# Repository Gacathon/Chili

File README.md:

# Lisence

CC BY-NC-SA 3.0

# Chili
Cherry G80-3000 Keyboard layout

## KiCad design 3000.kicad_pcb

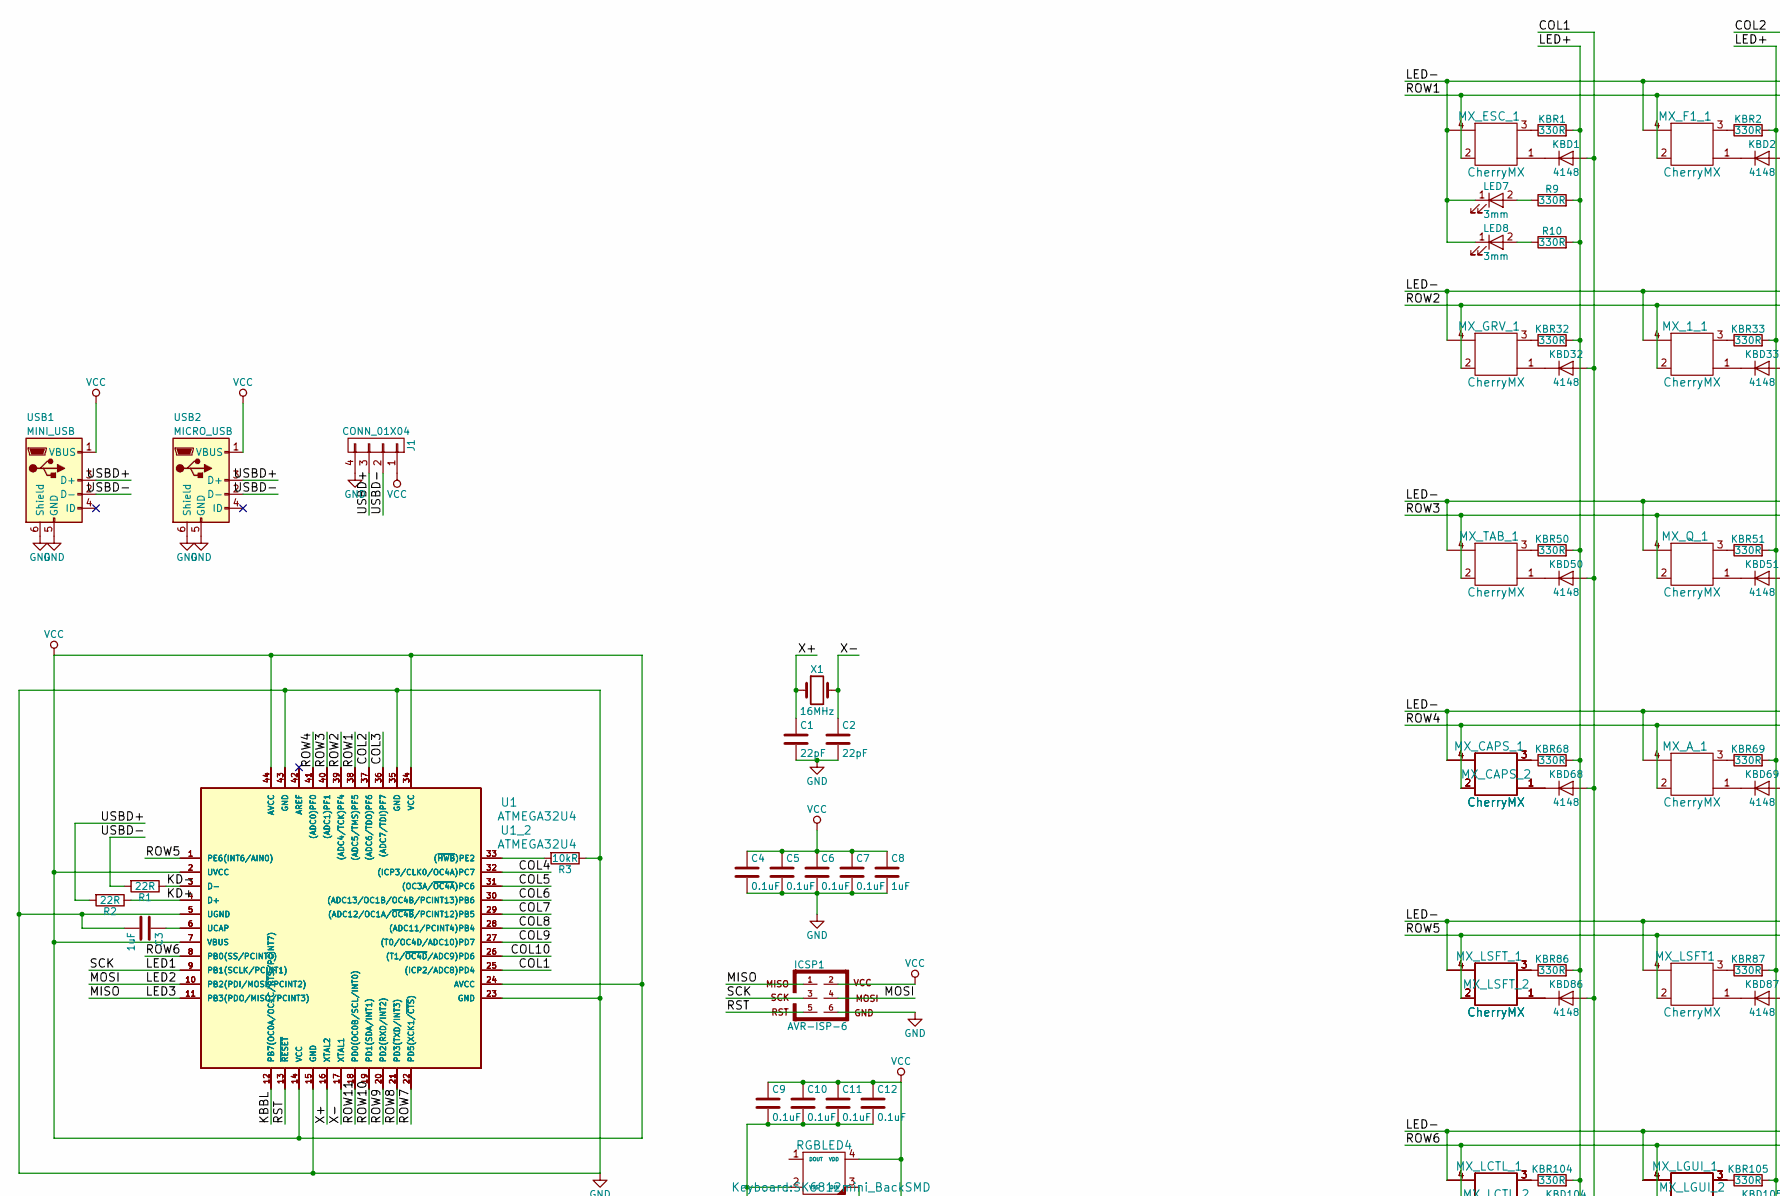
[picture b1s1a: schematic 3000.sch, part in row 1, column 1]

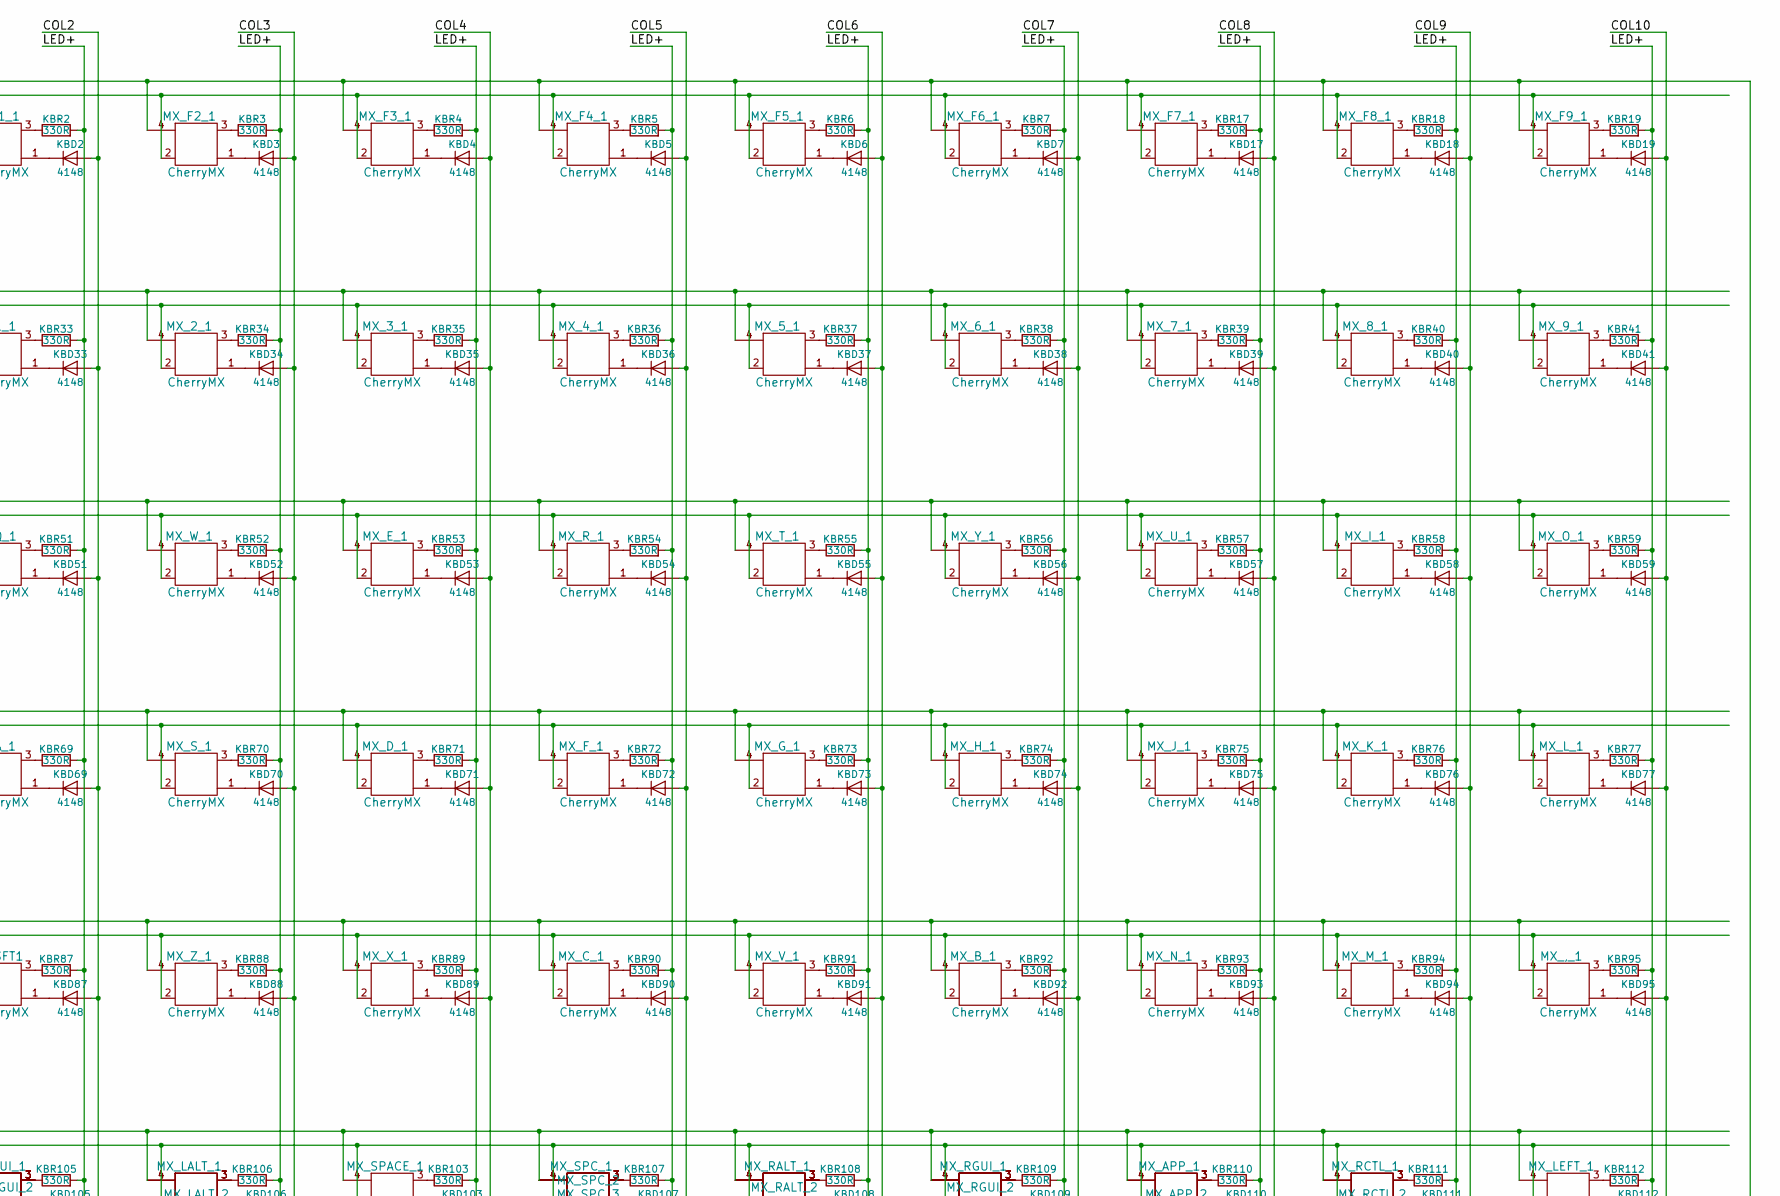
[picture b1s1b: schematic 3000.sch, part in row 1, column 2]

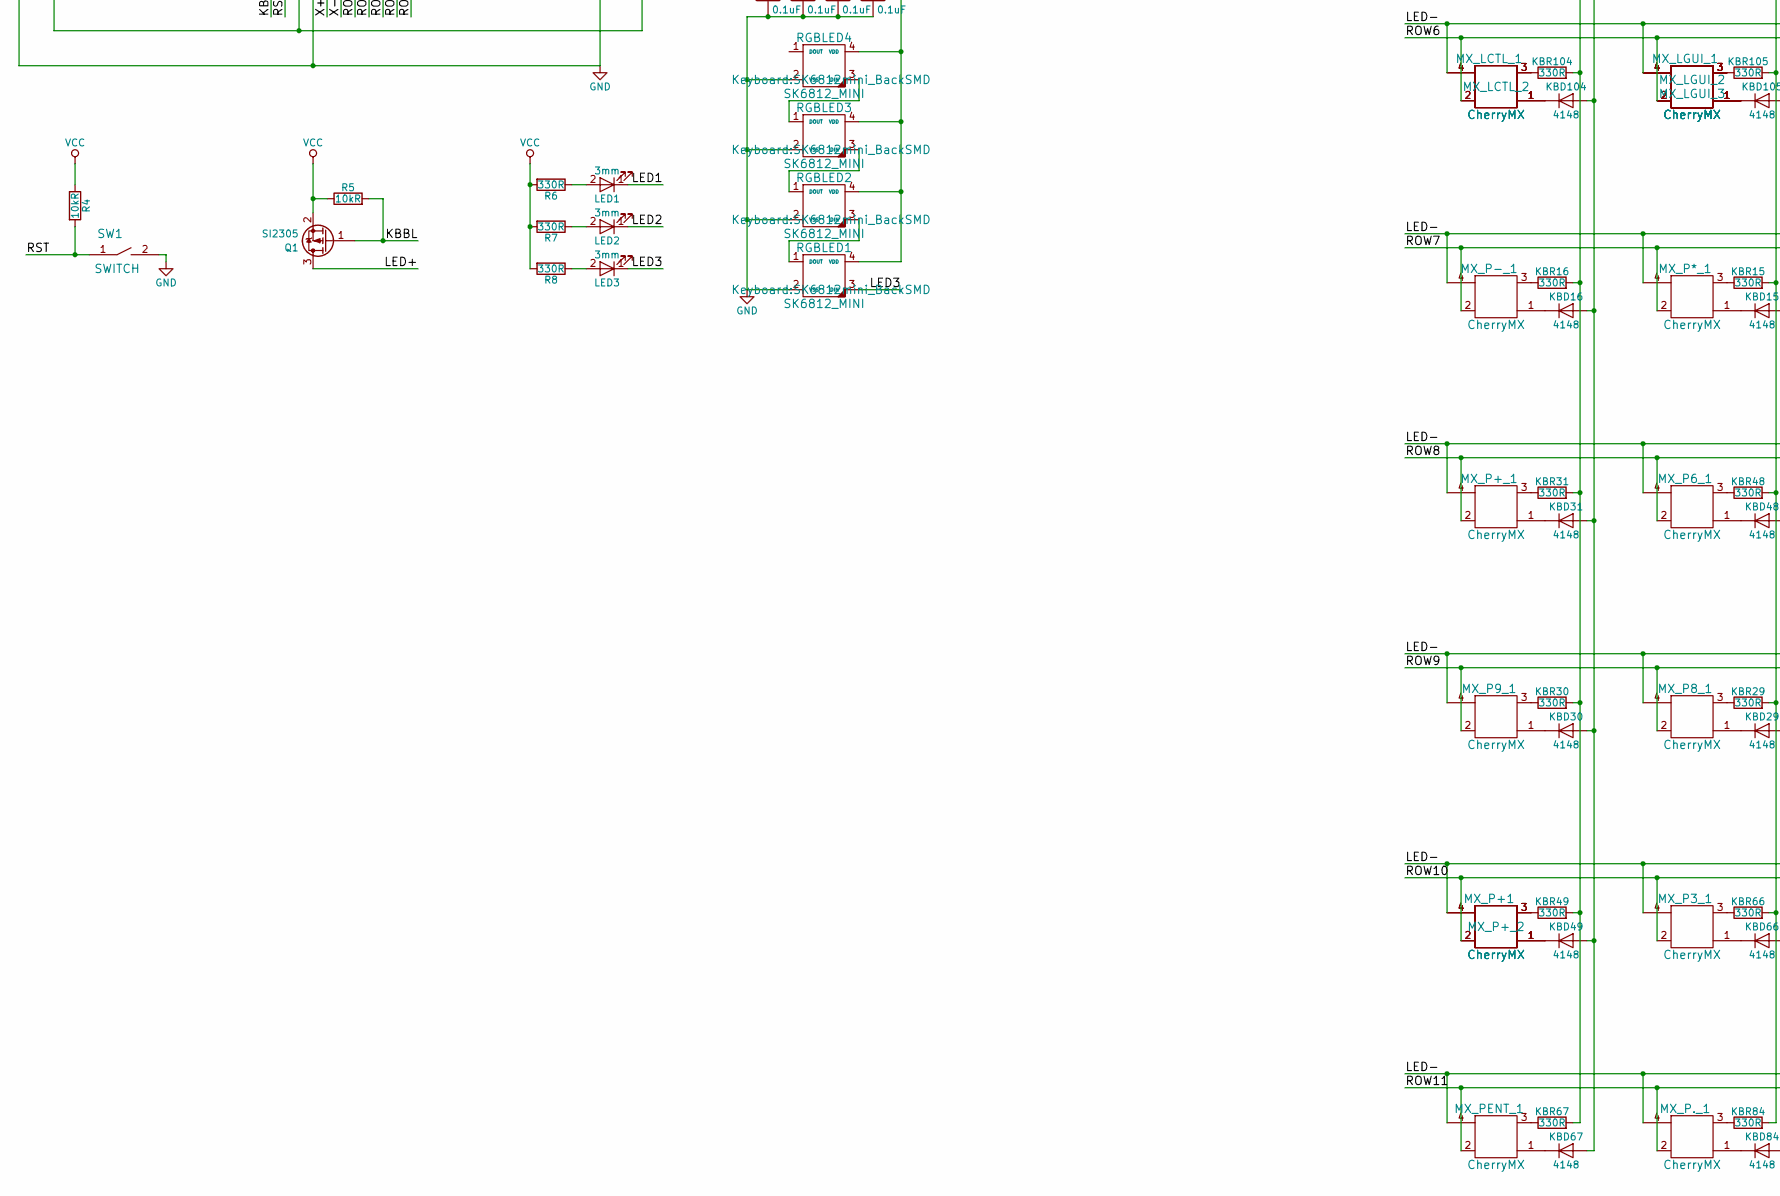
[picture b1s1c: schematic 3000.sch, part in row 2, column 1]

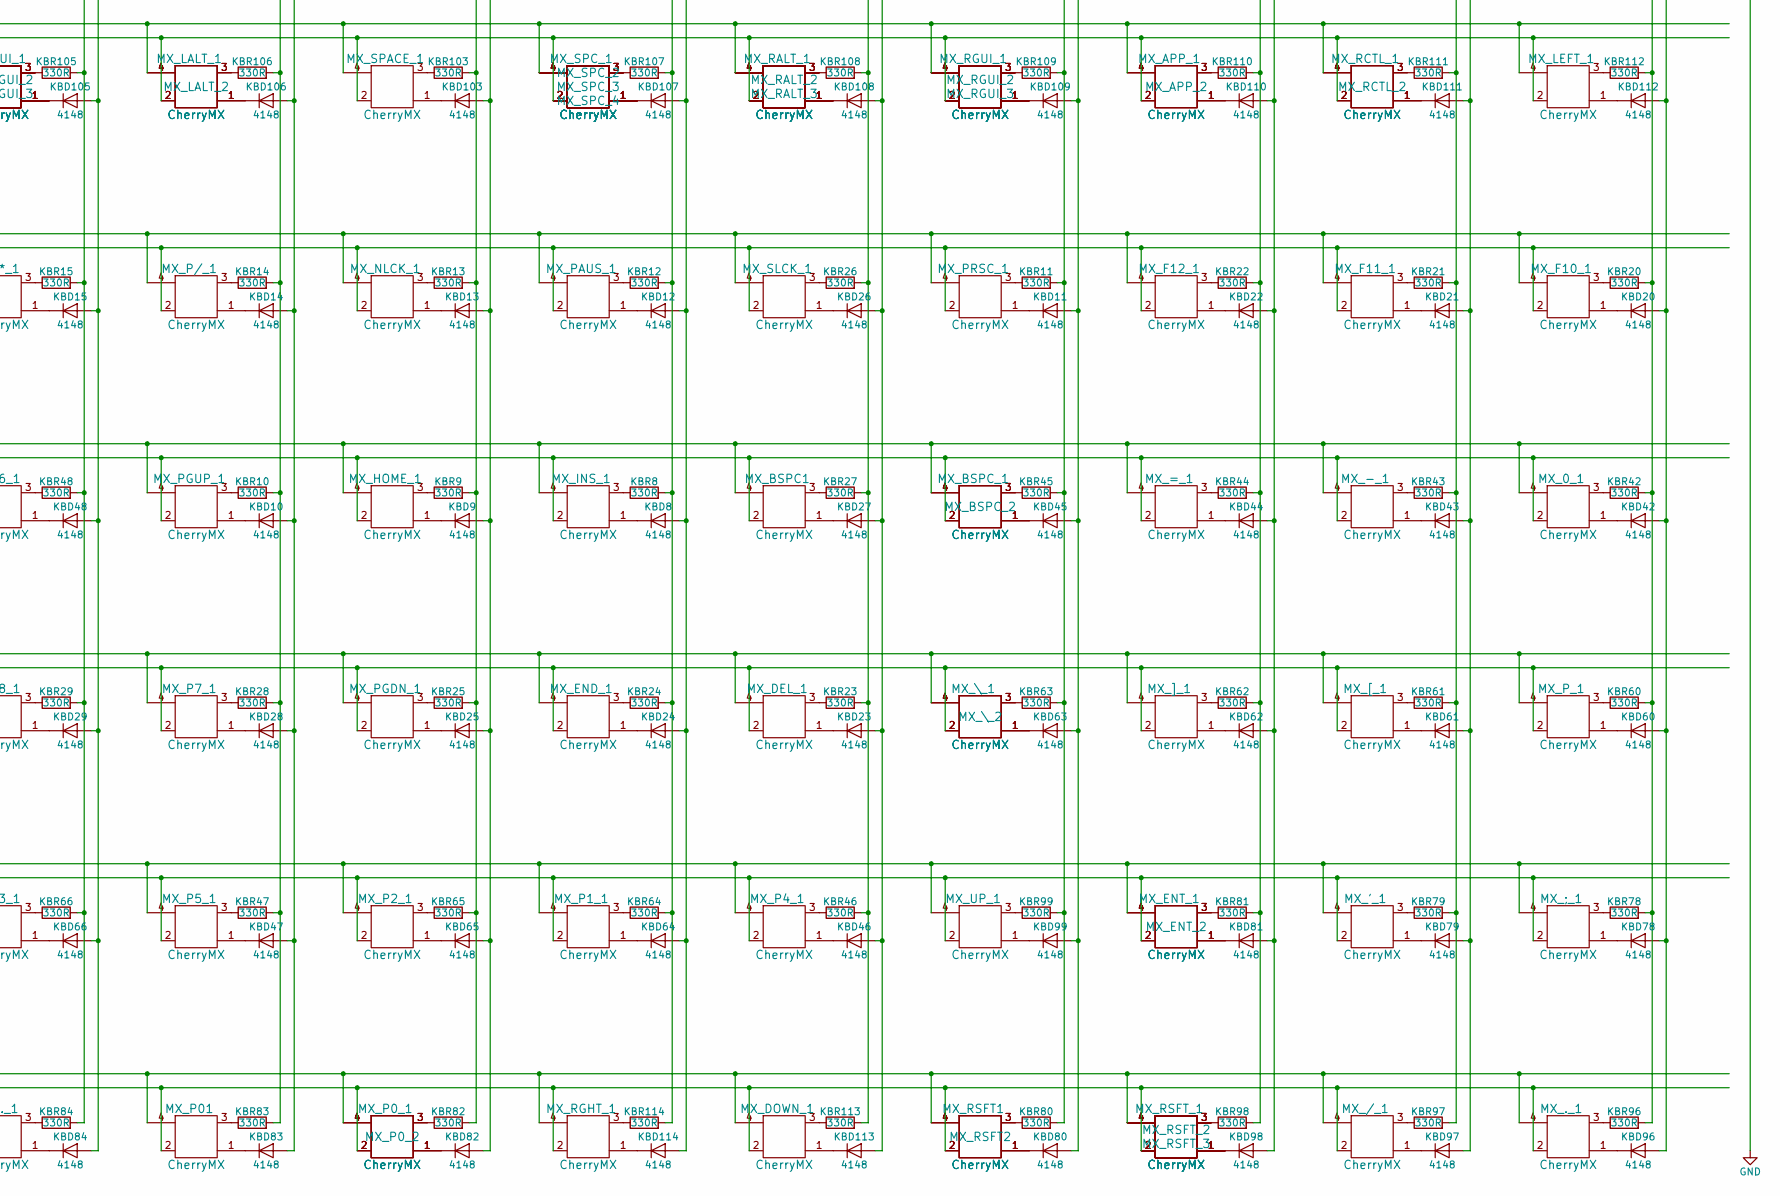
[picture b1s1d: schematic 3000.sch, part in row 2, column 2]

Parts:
C1, C2: 22pF; C_0805
C3, C8: 1uF; C_0805
C4, C5, C6, C7, C9, C10, C11, C12: 0.1uF; C_0805
ICSP1: AVR-ISP-6; Pin_Header_Straight_2x03_Pitch2.54mm
J1: CONN_01X04; Pin_Header_Straight_1x04_Pitch2.54mm
KBD1, KBD2, KBD3, KBD4, KBD5, KBD6, KBD7, KBD8, KBD9, KBD10, KBD11, KBD12, KBD13, KBD14, KBD15, KBD16, KBD17, KBD18, KBD19, KBD20, KBD21, KBD22, KBD23, KBD24, KBD25, KBD26, KBD27, KBD28, KBD29, KBD30, KBD31, KBD32, KBD33, KBD34, KBD35, KBD36, KBD37, KBD38, KBD39, KBD40, KBD41, KBD42, KBD43, KBD44, KBD45, KBD46, KBD47, KBD48, KBD49, KBD50, KBD51, KBD52, KBD53, KBD54, KBD55, KBD56, KBD57, KBD58, KBD59, KBD60, KBD61, KBD62, KBD63, KBD64, KBD65, KBD66, KBD67, KBD68, KBD69, KBD70, KBD71, KBD72, KBD73, KBD74, KBD75, KBD76, KBD77, KBD78, KBD79, KBD80, KBD81, KBD82, KBD83, KBD84, KBD86, KBD87, KBD88, KBD89, KBD90, KBD91, KBD92, KBD93, KBD94, KBD95, KBD96, KBD97, KBD98, KBD99, KBD103, KBD104, KBD105, KBD106, KBD107, KBD108, KBD109, KBD110, KBD111, KBD112, KBD113, KBD114: 4148; D_0805
KBR1, KBR2, KBR3, KBR4, KBR5, KBR6, KBR7, KBR8, KBR9, KBR10, KBR11, KBR12, KBR13, KBR14, KBR15, KBR16, KBR17, KBR18, KBR19, KBR20, KBR21, KBR22, KBR23, KBR24, KBR25, KBR26, KBR27, KBR28, KBR29, KBR30, KBR31, KBR32, KBR33, KBR34, KBR35, KBR36, KBR37, KBR38, KBR39, KBR40, KBR41, KBR42, KBR43, KBR44, KBR45, KBR46, KBR47, KBR48, KBR49, KBR50, KBR51, KBR52, KBR53, KBR54, KBR55, KBR56, KBR57, KBR58, KBR59, KBR60, KBR61, KBR62, KBR63, KBR64, KBR65, KBR66, KBR67, KBR68, KBR69, KBR70, KBR71, KBR72, KBR73, KBR74, KBR75, KBR76, KBR77, KBR78, KBR79, KBR80, KBR81, KBR82, KBR83, KBR84, KBR86, KBR87, KBR88, KBR89, KBR90, KBR91, KBR92, KBR93, KBR94, KBR95, KBR96, KBR97, KBR98, KBR99, KBR103, KBR104, KBR105, KBR106, KBR107, KBR108, KBR109, KBR110, KBR111, KBR112, KBR113, KBR114: 330R; R_0805
LED1, LED2, LED3, LED7, LED8: 3mm; LED_D3.0mm
MX_0_1, MX_1_1, MX_2_1, MX_3_1, MX_4_1, MX_5_1, MX_6_1, MX_7_1, MX_8_1, MX_9_1, MX_._1: CherryMX; MX1A&LED
MX_'_1: CherryMX; MX1A&LED
MX_,_1: CherryMX; MX1A&LED
MX_-_1: CherryMX; MX1A&LED
MX_/_1: CherryMX; MX1A&LED
MX_;_1: CherryMX; MX1A&LED
MX_=_1: CherryMX; MX1A&LED
MX_APP_1, MX_APP_2: CherryMX; MX1A&LED
MX_A_1: CherryMX; MX1A&LED
MX_BSPC1: CherryMX; MX1A&LED
MX_BSPC_1, MX_BSPC_2: CherryMX; MX1A&LED
MX_B_1: CherryMX; MX1A&LED
MX_CAPS_1, MX_CAPS_2: CherryMX; MX1A&LED
MX_C_1: CherryMX; MX1A&LED
MX_DEL_1: CherryMX; MX1A&LED
MX_DOWN_1: CherryMX; MX1A&LED
MX_D_1: CherryMX; MX1A&LED
MX_END_1: CherryMX; MX1A&LED
MX_ENT_1, MX_ENT_2: CherryMX; MX1A&LED
MX_ESC_1: CherryMX; MX1A&LED
MX_E_1: CherryMX; MX1A&LED
MX_F1_1, MX_F2_1, MX_F3_1, MX_F4_1, MX_F5_1, MX_F6_1, MX_F7_1, MX_F8_1, MX_F9_1, MX_F10_1, MX_F11_1, MX_F12_1: CherryMX; MX1A&LED
MX_F_1: CherryMX; MX1A&LED
MX_GRV_1: CherryMX; MX1A&LED
MX_G_1: CherryMX; MX1A&LED
MX_HOME_1: CherryMX; MX1A&LED
MX_H_1: CherryMX; MX1A&LED
MX_INS_1: CherryMX; MX1A&LED
MX_I_1: CherryMX; MX1A&LED
MX_J_1: CherryMX; MX1A&LED
MX_K_1: CherryMX; MX1A&LED
MX_LALT_1, MX_LALT_2: CherryMX; MX1A&LED
MX_LCTL_1, MX_LCTL_2: CherryMX; MX1A&LED
MX_LEFT_1: CherryMX; MX1A&LED
MX_LGUI_1, MX_LGUI_2, MX_LGUI_3: CherryMX; MX1A&LED
MX_LSFT1: CherryMX; MX1A&LED
MX_LSFT_1, MX_LSFT_2: CherryMX; MX1A&LED
MX_L_1: CherryMX; MX1A&LED
MX_M_1: CherryMX; MX1A&LED
MX_NLCK_1: CherryMX; MX1A&LED
MX_N_1: CherryMX; MX1A&LED
MX_O_1: CherryMX; MX1A&LED
MX_P0_1, MX_P0_2, MX_P01, MX_P1_1, MX_P2_1, MX_P3_1, MX_P4_1, MX_P5_1, MX_P6_1, MX_P7_1, MX_P8_1, MX_P9_1, MX_P._1: CherryMX; MX1A&LED
MX_P*_1: CherryMX; MX1A&LED
MX_P+1: CherryMX; MX1A&LED
MX_P+_1, MX_P+_2: CherryMX; MX1A&LED
MX_P-_1: CherryMX; MX1A&LED
MX_P/_1: CherryMX; MX1A&LED
MX_PAUS_1: CherryMX; MX1A&LED
MX_PENT_1: CherryMX; MX1A&LED
MX_PGDN_1: CherryMX; MX1A&LED
MX_PGUP_1: CherryMX; MX1A&LED
MX_PRSC_1: CherryMX; MX1A&LED
MX_P_1: CherryMX; MX1A&LED
MX_Q_1: CherryMX; MX1A&LED
MX_RALT_1, MX_RALT_2, MX_RALT_3: CherryMX; MX1A&LED
MX_RCTL_1, MX_RCTL_2: CherryMX; MX1A&LED
MX_RGHT_1: CherryMX; MX1A&LED
MX_RGUI_1, MX_RGUI_2, MX_RGUI_3: CherryMX; MX1A&LED
MX_RSFT1, MX_RSFT2: CherryMX; MX1A&LED
MX_RSFT_1, MX_RSFT_2, MX_RSFT_3: CherryMX; MX1A&LED
MX_R_1: CherryMX; MX1A&LED
MX_SLCK_1: CherryMX; MX1A&LED
MX_SPACE_1: CherryMX; MX1A&LED
MX_SPC_1, MX_SPC_2, MX_SPC_3, MX_SPC_4: CherryMX; MX1A&LED
MX_S_1: CherryMX; MX1A&LED
MX_TAB_1: CherryMX; MX1A&LED
MX_T_1: CherryMX; MX1A&LED
MX_UP_1: CherryMX; MX1A&LED
MX_U_1: CherryMX; MX1A&LED
MX_V_1: CherryMX; MX1A&LED
MX_W_1: CherryMX; MX1A&LED
MX_X_1: CherryMX; MX1A&LED
MX_Y_1: CherryMX; MX1A&LED
MX_Z_1: CherryMX; MX1A&LED
MX_[_1: CherryMX; MX1A&LED
MX_\_1, MX_\_2: CherryMX; MX1A&LED
MX_]_1: CherryMX; MX1A&LED
Q1: SI2305; SOT-23
R1, R2: 22R; R_0805
R3, R4, R5: 10kR; R_0805
R6, R7, R8, R9, R10: 330R; R_0805
RGBLED1, RGBLED2, RGBLED3, RGBLED4: SK6812_MINI; SK6812mini_BackSMD
SW1: SWITCH; SWITCH-3X6X2.5_SMD+
U1: ATMEGA32U4; TQFP-44_10x10mm_Pitch0.8mm
U1_2: ATMEGA32U4; QFN-44_7x7mm_Pitch0.5mm
USB1: MINI_USB; USB_MINI_4FOOT
USB2: MICRO_USB; USB_MICRO_4FOOT
X1: 16MHz; X_SMD_5032-2pin_5.0x3.2mm

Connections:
/COL1: KBD1.2 (A), KBD16.2 (A), KBD30.2 (A), KBD31.2 (A), KBD32.2 (A), KBD49.2 (A), KBD50.2 (A), KBD67.2 (A), KBD68.2 (A), KBD86.2 (A), KBD104.2 (A), U1.25 ((ICP2/ADC8)PD4), U1_2.25 ((ICP2/ADC8)PD4)
/COL2: KBD2.2 (A), KBD15.2 (A), KBD29.2 (A), KBD33.2 (A), KBD48.2 (A), KBD51.2 (A), KBD66.2 (A), KBD69.2 (A), KBD84.2 (A), KBD87.2 (A), KBD105.2 (A), U1.37 ((ADC6/TDO)PF6), U1_2.37 ((ADC6/TDO)PF6)
/COL3: KBD3.2 (A), KBD10.2 (A), KBD14.2 (A), KBD28.2 (A), KBD34.2 (A), KBD47.2 (A), KBD52.2 (A), KBD70.2 (A), KBD83.2 (A), KBD88.2 (A), KBD106.2 (A), U1.36 ((ADC7/TDI)PF7), U1_2.36 ((ADC7/TDI)PF7)
/COL4: KBD4.2 (A), KBD9.2 (A), KBD13.2 (A), KBD25.2 (A), KBD35.2 (A), KBD53.2 (A), KBD65.2 (A), KBD71.2 (A), KBD82.2 (A), KBD89.2 (A), KBD103.2 (A), U1.32 ((ICP3/CLK0/OC4A)PC7), U1_2.32 ((ICP3/CLK0/OC4A)PC7)
/COL5: KBD5.2 (A), KBD8.2 (A), KBD12.2 (A), KBD24.2 (A), KBD36.2 (A), KBD54.2 (A), KBD64.2 (A), KBD72.2 (A), KBD90.2 (A), KBD107.2 (A), KBD114.2 (A), U1.31 ((OC3A/~OC4A~)PC6), U1_2.31 ((OC3A/~OC4A~)PC6)
/COL6: KBD6.2 (A), KBD23.2 (A), KBD26.2 (A), KBD27.2 (A), KBD37.2 (A), KBD46.2 (A), KBD55.2 (A), KBD73.2 (A), KBD91.2 (A), KBD108.2 (A), KBD113.2 (A), U1.30 ((ADC13/OC1B/OC4B/PCINT13)PB6), U1_2.30 ((ADC13/OC1B/OC4B/PCINT13)PB6)
/COL7: KBD7.2 (A), KBD11.2 (A), KBD38.2 (A), KBD45.2 (A), KBD56.2 (A), KBD63.2 (A), KBD74.2 (A), KBD80.2 (A), KBD92.2 (A), KBD99.2 (A), KBD109.2 (A), U1.29 ((ADC12/OC1A/~OC4B~/PCINT12)PB5), U1_2.29 ((ADC12/OC1A/~OC4B~/PCINT12)PB5)
/COL8: KBD17.2 (A), KBD22.2 (A), KBD39.2 (A), KBD44.2 (A), KBD57.2 (A), KBD62.2 (A), KBD75.2 (A), KBD81.2 (A), KBD93.2 (A), KBD98.2 (A), KBD110.2 (A), U1.28 ((ADC11/PCINT4)PB4), U1_2.28 ((ADC11/PCINT4)PB4)
/COL9: KBD18.2 (A), KBD21.2 (A), KBD40.2 (A), KBD43.2 (A), KBD58.2 (A), KBD61.2 (A), KBD76.2 (A), KBD79.2 (A), KBD94.2 (A), KBD97.2 (A), KBD111.2 (A), U1.27 ((T0/OC4D/ADC10)PD7), U1_2.27 ((T0/OC4D/ADC10)PD7)
/COL10: KBD19.2 (A), KBD20.2 (A), KBD41.2 (A), KBD42.2 (A), KBD59.2 (A), KBD60.2 (A), KBD77.2 (A), KBD78.2 (A), KBD95.2 (A), KBD96.2 (A), KBD112.2 (A), U1.26 ((T1/~OC4D~/ADC9)PD6), U1_2.26 ((T1/~OC4D~/ADC9)PD6)
/KBBL: Q1.1 (G), R5.2, U1.12 (PB7(OC0A/OC1C/~RTS~/PCINT7)), U1_2.12 (PB7(OC0A/OC1C/~RTS~/PCINT7))
/KD+: R2.1, U1.4 (D+), U1_2.4 (D+)
/KD-: R1.1, U1.3 (D-), U1_2.3 (D-)
/LED1: ICSP1.3, LED1.1 (K), U1.9 (PB1(SCLK/PCINT1)), U1_2.9 (PB1(SCLK/PCINT1)); also elsewhere on the board
/LED2: ICSP1.4, LED2.1 (K), U1.10 (PB2(PDI/MOSI/PCINT2)), U1_2.10 (PB2(PDI/MOSI/PCINT2)); also elsewhere on the board
/LED3: ICSP1.1, LED3.1 (K), RGBLED1.3 (DIN), U1.11 (PB3(PDO/MISO/PCINT3)), U1_2.11 (PB3(PDO/MISO/PCINT3)); also elsewhere on the board
/LED+: KBR1.2, KBR2.2, KBR3.2, KBR4.2, KBR5.2, KBR6.2, KBR7.2, KBR8.2, KBR9.2, KBR10.2, KBR11.2, KBR12.2, KBR13.2, KBR14.2, KBR15.2, KBR16.2, KBR17.2, KBR18.2, KBR19.2, KBR20.2, KBR21.2, KBR22.2, KBR23.2, KBR24.2, KBR25.2, KBR26.2, KBR27.2, KBR28.2, KBR29.2, KBR30.2, KBR31.2, KBR32.2, KBR33.2, KBR34.2, KBR35.2, KBR36.2, KBR37.2, KBR38.2, KBR39.2, KBR40.2, KBR41.2, KBR42.2, KBR43.2, KBR44.2, KBR45.2, KBR46.2, KBR47.2, KBR48.2, KBR49.2, KBR50.2, KBR51.2, KBR52.2, KBR53.2, KBR54.2, KBR55.2, KBR56.2, KBR57.2, KBR58.2, KBR59.2, KBR60.2, KBR61.2, KBR62.2, KBR63.2, KBR64.2, KBR65.2, KBR66.2, KBR67.2, KBR68.2, KBR69.2, KBR70.2, KBR71.2, KBR72.2, KBR73.2, KBR74.2, KBR75.2, KBR76.2, KBR77.2, KBR78.2, KBR79.2, KBR80.2, KBR81.2, KBR82.2, KBR83.2, KBR84.2, KBR86.2, KBR87.2, KBR88.2, KBR89.2, KBR90.2, KBR91.2, KBR92.2, KBR93.2, KBR94.2, KBR95.2, KBR96.2, KBR97.2, KBR98.2, KBR99.2, KBR103.2, KBR104.2, KBR105.2, KBR106.2, KBR107.2, KBR108.2, KBR109.2, KBR110.2, KBR111.2, KBR112.2, KBR113.2, KBR114.2, Q1.3 (D), R9.2, R10.2
/ROW1: MX_ESC_1.2, MX_F1_1.2, MX_F2_1.2, MX_F3_1.2, MX_F4_1.2, MX_F5_1.2, MX_F6_1.2, MX_F7_1.2, MX_F8_1.2, MX_F9_1.2, U1.38 ((ADC5/TMS)PF5), U1_2.38 ((ADC5/TMS)PF5)
/ROW2: MX_1_1.2, MX_2_1.2, MX_3_1.2, MX_4_1.2, MX_5_1.2, MX_6_1.2, MX_7_1.2, MX_8_1.2, MX_9_1.2, MX_GRV_1.2, U1.39 ((ADC4/TCK)PF4), U1_2.39 ((ADC4/TCK)PF4)
/ROW3: MX_E_1.2, MX_I_1.2, MX_O_1.2, MX_Q_1.2, MX_R_1.2, MX_TAB_1.2, MX_T_1.2, MX_U_1.2, MX_W_1.2, MX_Y_1.2, U1.40 ((ADC1)PF1), U1_2.40 ((ADC1)PF1)
/ROW4: MX_A_1.2, MX_CAPS_1.2, MX_CAPS_2.2, MX_D_1.2, MX_F_1.2, MX_G_1.2, MX_H_1.2, MX_J_1.2, MX_K_1.2, MX_L_1.2, MX_S_1.2, U1.41 ((ADC0)PF0), U1_2.41 ((ADC0)PF0)
/ROW5: MX_,_1.2, MX_B_1.2, MX_C_1.2, MX_LSFT1.2, MX_LSFT_1.2, MX_LSFT_2.2, MX_M_1.2, MX_N_1.2, MX_V_1.2, MX_X_1.2, MX_Z_1.2, U1.1 (PE6(INT6/AIN0)), U1_2.1 (PE6(INT6/AIN0))
/ROW6: MX_APP_1.2, MX_APP_2.2, MX_LALT_1.2, MX_LALT_2.2, MX_LCTL_1.2, MX_LCTL_2.2, MX_LEFT_1.2, MX_LGUI_1.2, MX_LGUI_2.2, MX_LGUI_3.2, MX_RALT_1.2, MX_RALT_2.2, MX_RALT_3.2, MX_RCTL_1.2, MX_RCTL_2.2, MX_RGUI_1.2, MX_RGUI_2.2, MX_RGUI_3.2, MX_SPACE_1.2, MX_SPC_1.2, MX_SPC_2.2, MX_SPC_3.2, MX_SPC_4.2, U1.8 (PB0(SS/PCINT0)), U1_2.8 (PB0(SS/PCINT0))
/ROW7: MX_F10_1.2, MX_F11_1.2, MX_F12_1.2, MX_NLCK_1.2, MX_P*_1.2, MX_P-_1.2, MX_P/_1.2, MX_PAUS_1.2, MX_PRSC_1.2, MX_SLCK_1.2, U1.22 (PD5(XCK1/~CTS~)), U1_2.22 (PD5(XCK1/~CTS~))
/ROW8: MX_0_1.2, MX_-_1.2, MX_=_1.2, MX_BSPC1.2, MX_BSPC_1.2, MX_BSPC_2.2, MX_HOME_1.2, MX_INS_1.2, MX_P6_1.2, MX_P+_1.2, MX_PGUP_1.2, U1.21 (PD3(TXD/INT3)), U1_2.21 (PD3(TXD/INT3))
/ROW9: MX_DEL_1.2, MX_END_1.2, MX_P7_1.2, MX_P8_1.2, MX_P9_1.2, MX_PGDN_1.2, MX_P_1.2, MX_[_1.2, MX_\_1.2, MX_\_2.2, MX_]_1.2, U1.20 (PD2(RXD/INT2)), U1_2.20 (PD2(RXD/INT2))
/ROW10: MX_'_1.2, MX_;_1.2, MX_ENT_1.2, MX_ENT_2.2, MX_P1_1.2, MX_P2_1.2, MX_P3_1.2, MX_P4_1.2, MX_P5_1.2, MX_P+1.2, MX_P+_2.2, MX_UP_1.2, U1.19 (PD1(SDA/INT1)), U1_2.19 (PD1(SDA/INT1))
/ROW11: MX_._1.2, MX_/_1.2, MX_DOWN_1.2, MX_P0_1.2, MX_P0_2.2, MX_P01.2, MX_P._1.2, MX_PENT_1.2, MX_RGHT_1.2, MX_RSFT1.2, MX_RSFT2.2, MX_RSFT_1.2, MX_RSFT_2.2, MX_RSFT_3.2, U1.18 (PD0(OC0B/SCL/INT0)), U1_2.18 (PD0(OC0B/SCL/INT0))
/RST: ICSP1.5, R4.2, SW1.1, U1.13 (~RESET~), U1_2.13 (~RESET~)
/USBD+: J1.3, R2.2, USB1.3 (D+), USB2.3 (D+)
/USBD-: J1.2, R1.2, USB1.2 (D-), USB2.2 (D-)
/X+: C1.1, U1.16 (XTAL2), U1_2.16 (XTAL2), X1.1
/X-: C2.1, U1.17 (XTAL1), U1_2.17 (XTAL1), X1.2
GND: C1.2, C2.2, C3.2, C4.2, C5.2, C6.2, C7.2, C8.2, C9.2, C10.2, C11.2, C12.2, ICSP1.6, J1.4, LED7.1 (K), LED8.1 (K), MX_0_1.4, MX_1_1.4, MX_2_1.4, MX_3_1.4, MX_4_1.4, MX_5_1.4, MX_6_1.4, MX_7_1.4, MX_8_1.4, MX_9_1.4, MX_'_1.4, MX_,_1.4, MX_-_1.4, MX_._1.4, MX_/_1.4, MX_;_1.4, MX_=_1.4, MX_APP_1.4, MX_APP_2.4, MX_A_1.4, MX_BSPC1.4, MX_BSPC_1.4, MX_BSPC_2.4, MX_B_1.4, MX_CAPS_1.4, MX_CAPS_2.4, MX_C_1.4, MX_DEL_1.4, MX_DOWN_1.4, MX_D_1.4, MX_END_1.4, MX_ENT_1.4, MX_ENT_2.4, MX_ESC_1.4, MX_E_1.4, MX_F1_1.4, MX_F2_1.4, MX_F3_1.4, MX_F4_1.4, MX_F5_1.4, MX_F6_1.4, MX_F7_1.4, MX_F8_1.4, MX_F9_1.4, MX_F10_1.4, MX_F11_1.4, MX_F12_1.4, MX_F_1.4, MX_GRV_1.4, MX_G_1.4, MX_HOME_1.4, MX_H_1.4, MX_INS_1.4, MX_I_1.4, MX_J_1.4, MX_K_1.4, MX_LALT_1.4, MX_LALT_2.4, MX_LCTL_1.4, MX_LCTL_2.4, MX_LEFT_1.4, MX_LGUI_1.4, MX_LGUI_2.4, MX_LGUI_3.4, MX_LSFT1.4, MX_LSFT_1.4, MX_LSFT_2.4, MX_L_1.4, MX_M_1.4, MX_NLCK_1.4, MX_N_1.4, MX_O_1.4, MX_P0_1.4, MX_P0_2.4, MX_P01.4, MX_P1_1.4, MX_P2_1.4, MX_P3_1.4, MX_P4_1.4, MX_P5_1.4, MX_P6_1.4, MX_P7_1.4, MX_P8_1.4, MX_P9_1.4, MX_P*_1.4, MX_P+1.4, MX_P+_1.4, MX_P+_2.4, MX_P-_1.4, MX_P._1.4, MX_P/_1.4, MX_PAUS_1.4, MX_PENT_1.4, MX_PGDN_1.4, MX_PGUP_1.4, MX_PRSC_1.4, MX_P_1.4, MX_Q_1.4, MX_RALT_1.4, MX_RALT_2.4, MX_RALT_3.4, MX_RCTL_1.4, MX_RCTL_2.4, MX_RGHT_1.4, MX_RGUI_1.4, MX_RGUI_2.4, MX_RGUI_3.4, MX_RSFT1.4, MX_RSFT2.4, MX_RSFT_1.4, MX_RSFT_2.4, MX_RSFT_3.4, MX_R_1.4, MX_SLCK_1.4, MX_SPACE_1.4, MX_SPC_1.4, MX_SPC_2.4, MX_SPC_3.4, MX_SPC_4.4, MX_S_1.4, MX_TAB_1.4, MX_T_1.4, MX_UP_1.4, MX_U_1.4, MX_V_1.4, MX_W_1.4, MX_X_1.4, MX_Y_1.4, MX_Z_1.4, MX_[_1.4, MX_\_1.4, MX_\_2.4, MX_]_1.4, R3.1, RGBLED1.2 (VSS), RGBLED2.2 (VSS), RGBLED3.2 (VSS), RGBLED4.2 (VSS), SW1.2, U1.5 (UGND), U1.15 (GND), U1.23 (GND), U1.35 (GND), U1.43 (GND), U1_2.5 (UGND), U1_2.15 (GND), U1_2.23 (GND), U1_2.35 (GND), U1_2.43 (GND), USB1.5 (GND), USB1.6 (Shield), USB2.5 (GND), USB2.6 (Shield); also elsewhere on the board
unnamed: C3.1, U1.6 (UCAP), U1_2.6 (UCAP)
unnamed: KBD1.1 (K), MX_ESC_1.1
unnamed: KBD2.1 (K), MX_F1_1.1
unnamed: KBD3.1 (K), MX_F2_1.1
unnamed: KBD4.1 (K), MX_F3_1.1
unnamed: KBD5.1 (K), MX_F4_1.1
unnamed: KBD6.1 (K), MX_F5_1.1
unnamed: KBD7.1 (K), MX_F6_1.1
unnamed: KBD8.1 (K), MX_INS_1.1
unnamed: KBD9.1 (K), MX_HOME_1.1
unnamed: KBD10.1 (K), MX_PGUP_1.1
unnamed: KBD11.1 (K), MX_PRSC_1.1
unnamed: KBD12.1 (K), MX_PAUS_1.1
unnamed: KBD13.1 (K), MX_NLCK_1.1
unnamed: KBD14.1 (K), MX_P/_1.1
unnamed: KBD15.1 (K), MX_P*_1.1
unnamed: KBD16.1 (K), MX_P-_1.1
unnamed: KBD17.1 (K), MX_F7_1.1
unnamed: KBD18.1 (K), MX_F8_1.1
unnamed: KBD19.1 (K), MX_F9_1.1
unnamed: KBD20.1 (K), MX_F10_1.1
unnamed: KBD21.1 (K), MX_F11_1.1
unnamed: KBD22.1 (K), MX_F12_1.1
unnamed: KBD23.1 (K), MX_DEL_1.1
unnamed: KBD24.1 (K), MX_END_1.1
unnamed: KBD25.1 (K), MX_PGDN_1.1
unnamed: KBD26.1 (K), MX_SLCK_1.1
unnamed: KBD27.1 (K), MX_BSPC1.1
unnamed: KBD28.1 (K), MX_P7_1.1
unnamed: KBD29.1 (K), MX_P8_1.1
unnamed: KBD30.1 (K), MX_P9_1.1
unnamed: KBD31.1 (K), MX_P+_1.1
unnamed: KBD32.1 (K), MX_GRV_1.1
unnamed: KBD33.1 (K), MX_1_1.1
unnamed: KBD34.1 (K), MX_2_1.1
unnamed: KBD35.1 (K), MX_3_1.1
unnamed: KBD36.1 (K), MX_4_1.1
unnamed: KBD37.1 (K), MX_5_1.1
unnamed: KBD38.1 (K), MX_6_1.1
unnamed: KBD39.1 (K), MX_7_1.1
unnamed: KBD40.1 (K), MX_8_1.1
unnamed: KBD41.1 (K), MX_9_1.1
unnamed: KBD42.1 (K), MX_0_1.1
unnamed: KBD43.1 (K), MX_-_1.1
unnamed: KBD44.1 (K), MX_=_1.1
unnamed: KBD45.1 (K), MX_BSPC_1.1, MX_BSPC_2.1
unnamed: KBD46.1 (K), MX_P4_1.1
unnamed: KBD47.1 (K), MX_P5_1.1
unnamed: KBD48.1 (K), MX_P6_1.1
unnamed: KBD49.1 (K), MX_P+1.1, MX_P+_2.1
unnamed: KBD50.1 (K), MX_TAB_1.1
unnamed: KBD51.1 (K), MX_Q_1.1
unnamed: KBD52.1 (K), MX_W_1.1
unnamed: KBD53.1 (K), MX_E_1.1
unnamed: KBD54.1 (K), MX_R_1.1
unnamed: KBD55.1 (K), MX_T_1.1
unnamed: KBD56.1 (K), MX_Y_1.1
unnamed: KBD57.1 (K), MX_U_1.1
unnamed: KBD58.1 (K), MX_I_1.1
unnamed: KBD59.1 (K), MX_O_1.1
unnamed: KBD60.1 (K), MX_P_1.1
unnamed: KBD61.1 (K), MX_[_1.1
unnamed: KBD62.1 (K), MX_]_1.1
unnamed: KBD63.1 (K), MX_\_1.1, MX_\_2.1
unnamed: KBD64.1 (K), MX_P1_1.1
unnamed: KBD65.1 (K), MX_P2_1.1
unnamed: KBD66.1 (K), MX_P3_1.1
unnamed: KBD67.1 (K), MX_PENT_1.1
unnamed: KBD68.1 (K), MX_CAPS_1.1, MX_CAPS_2.1
unnamed: KBD69.1 (K), MX_A_1.1
unnamed: KBD70.1 (K), MX_S_1.1
unnamed: KBD71.1 (K), MX_D_1.1
unnamed: KBD72.1 (K), MX_F_1.1
unnamed: KBD73.1 (K), MX_G_1.1
unnamed: KBD74.1 (K), MX_H_1.1
unnamed: KBD75.1 (K), MX_J_1.1
unnamed: KBD76.1 (K), MX_K_1.1
unnamed: KBD77.1 (K), MX_L_1.1
unnamed: KBD78.1 (K), MX_;_1.1
unnamed: KBD79.1 (K), MX_'_1.1
unnamed: KBD80.1 (K), MX_RSFT1.1, MX_RSFT2.1
unnamed: KBD81.1 (K), MX_ENT_1.1, MX_ENT_2.1
unnamed: KBD82.1 (K), MX_P0_1.1, MX_P0_2.1
unnamed: KBD83.1 (K), MX_P01.1
unnamed: KBD84.1 (K), MX_P._1.1
unnamed: KBD86.1 (K), MX_LSFT_1.1, MX_LSFT_2.1
unnamed: KBD87.1 (K), MX_LSFT1.1
unnamed: KBD88.1 (K), MX_Z_1.1
unnamed: KBD89.1 (K), MX_X_1.1
unnamed: KBD90.1 (K), MX_C_1.1
unnamed: KBD91.1 (K), MX_V_1.1
unnamed: KBD92.1 (K), MX_B_1.1
unnamed: KBD93.1 (K), MX_N_1.1
unnamed: KBD94.1 (K), MX_M_1.1
unnamed: KBD95.1 (K), MX_,_1.1
unnamed: KBD96.1 (K), MX_._1.1
unnamed: KBD97.1 (K), MX_/_1.1
unnamed: KBD98.1 (K), MX_RSFT_1.1, MX_RSFT_2.1, MX_RSFT_3.1
unnamed: KBD99.1 (K), MX_UP_1.1
unnamed: KBD103.1 (K), MX_SPACE_1.1
unnamed: KBD104.1 (K), MX_LCTL_1.1, MX_LCTL_2.1
unnamed: KBD105.1 (K), MX_LGUI_1.1, MX_LGUI_2.1, MX_LGUI_3.1
unnamed: KBD106.1 (K), MX_LALT_1.1, MX_LALT_2.1
unnamed: KBD107.1 (K), MX_SPC_1.1, MX_SPC_2.1, MX_SPC_3.1, MX_SPC_4.1
unnamed: KBD108.1 (K), MX_RALT_1.1, MX_RALT_2.1, MX_RALT_3.1
unnamed: KBD109.1 (K), MX_RGUI_1.1, MX_RGUI_2.1, MX_RGUI_3.1
unnamed: KBD110.1 (K), MX_APP_1.1, MX_APP_2.1
unnamed: KBD111.1 (K), MX_RCTL_1.1, MX_RCTL_2.1
unnamed: KBD112.1 (K), MX_LEFT_1.1
unnamed: KBD113.1 (K), MX_DOWN_1.1
unnamed: KBD114.1 (K), MX_RGHT_1.1
unnamed: KBR1.1, MX_ESC_1.3
unnamed: KBR2.1, MX_F1_1.3
unnamed: KBR3.1, MX_F2_1.3
unnamed: KBR4.1, MX_F3_1.3
unnamed: KBR5.1, MX_F4_1.3
unnamed: KBR6.1, MX_F5_1.3
unnamed: KBR7.1, MX_F6_1.3
unnamed: KBR8.1, MX_INS_1.3
unnamed: KBR9.1, MX_HOME_1.3
unnamed: KBR10.1, MX_PGUP_1.3
unnamed: KBR11.1, MX_PRSC_1.3
unnamed: KBR12.1, MX_PAUS_1.3
unnamed: KBR13.1, MX_NLCK_1.3
unnamed: KBR14.1, MX_P/_1.3
unnamed: KBR15.1, MX_P*_1.3
unnamed: KBR16.1, MX_P-_1.3
unnamed: KBR17.1, MX_F7_1.3
unnamed: KBR18.1, MX_F8_1.3
unnamed: KBR19.1, MX_F9_1.3
unnamed: KBR20.1, MX_F10_1.3
unnamed: KBR21.1, MX_F11_1.3
unnamed: KBR22.1, MX_F12_1.3
unnamed: KBR23.1, MX_DEL_1.3
unnamed: KBR24.1, MX_END_1.3
unnamed: KBR25.1, MX_PGDN_1.3
unnamed: KBR26.1, MX_SLCK_1.3
unnamed: KBR27.1, MX_BSPC1.3
unnamed: KBR28.1, MX_P7_1.3
unnamed: KBR29.1, MX_P8_1.3
unnamed: KBR30.1, MX_P9_1.3
unnamed: KBR31.1, MX_P+_1.3
unnamed: KBR32.1, MX_GRV_1.3
unnamed: KBR33.1, MX_1_1.3
unnamed: KBR34.1, MX_2_1.3
unnamed: KBR35.1, MX_3_1.3
unnamed: KBR36.1, MX_4_1.3
unnamed: KBR37.1, MX_5_1.3
unnamed: KBR38.1, MX_6_1.3
unnamed: KBR39.1, MX_7_1.3
unnamed: KBR40.1, MX_8_1.3
unnamed: KBR41.1, MX_9_1.3
unnamed: KBR42.1, MX_0_1.3
unnamed: KBR43.1, MX_-_1.3
unnamed: KBR44.1, MX_=_1.3
unnamed: KBR45.1, MX_BSPC_1.3, MX_BSPC_2.3
unnamed: KBR46.1, MX_P4_1.3
unnamed: KBR47.1, MX_P5_1.3
unnamed: KBR48.1, MX_P6_1.3
unnamed: KBR49.1, MX_P+1.3, MX_P+_2.3
unnamed: KBR50.1, MX_TAB_1.3
unnamed: KBR51.1, MX_Q_1.3
unnamed: KBR52.1, MX_W_1.3
unnamed: KBR53.1, MX_E_1.3
unnamed: KBR54.1, MX_R_1.3
unnamed: KBR55.1, MX_T_1.3
unnamed: KBR56.1, MX_Y_1.3
unnamed: KBR57.1, MX_U_1.3
unnamed: KBR58.1, MX_I_1.3
unnamed: KBR59.1, MX_O_1.3
unnamed: KBR60.1, MX_P_1.3
unnamed: KBR61.1, MX_[_1.3
unnamed: KBR62.1, MX_]_1.3
unnamed: KBR63.1, MX_\_1.3, MX_\_2.3
unnamed: KBR64.1, MX_P1_1.3
unnamed: KBR65.1, MX_P2_1.3
unnamed: KBR66.1, MX_P3_1.3
unnamed: KBR67.1, MX_PENT_1.3
unnamed: KBR68.1, MX_CAPS_1.3, MX_CAPS_2.3
unnamed: KBR69.1, MX_A_1.3
unnamed: KBR70.1, MX_S_1.3
unnamed: KBR71.1, MX_D_1.3
unnamed: KBR72.1, MX_F_1.3
unnamed: KBR73.1, MX_G_1.3
unnamed: KBR74.1, MX_H_1.3
unnamed: KBR75.1, MX_J_1.3
unnamed: KBR76.1, MX_K_1.3
unnamed: KBR77.1, MX_L_1.3
unnamed: KBR78.1, MX_;_1.3
unnamed: KBR79.1, MX_'_1.3
unnamed: KBR80.1, MX_RSFT1.3, MX_RSFT2.3
unnamed: KBR81.1, MX_ENT_1.3, MX_ENT_2.3
unnamed: KBR82.1, MX_P0_1.3, MX_P0_2.3
unnamed: KBR83.1, MX_P01.3
unnamed: KBR84.1, MX_P._1.3
unnamed: KBR86.1, MX_LSFT_1.3, MX_LSFT_2.3
unnamed: KBR87.1, MX_LSFT1.3
unnamed: KBR88.1, MX_Z_1.3
unnamed: KBR89.1, MX_X_1.3
unnamed: KBR90.1, MX_C_1.3
unnamed: KBR91.1, MX_V_1.3
unnamed: KBR92.1, MX_B_1.3
unnamed: KBR93.1, MX_N_1.3
unnamed: KBR94.1, MX_M_1.3
unnamed: KBR95.1, MX_,_1.3
unnamed: KBR96.1, MX_._1.3
unnamed: KBR97.1, MX_/_1.3
unnamed: KBR98.1, MX_RSFT_1.3, MX_RSFT_2.3, MX_RSFT_3.3
unnamed: KBR99.1, MX_UP_1.3
unnamed: KBR103.1, MX_SPACE_1.3
unnamed: KBR104.1, MX_LCTL_1.3, MX_LCTL_2.3
unnamed: KBR105.1, MX_LGUI_1.3, MX_LGUI_2.3, MX_LGUI_3.3
unnamed: KBR106.1, MX_LALT_1.3, MX_LALT_2.3
unnamed: KBR107.1, MX_SPC_1.3, MX_SPC_2.3, MX_SPC_3.3, MX_SPC_4.3
unnamed: KBR108.1, MX_RALT_1.3, MX_RALT_2.3, MX_RALT_3.3
unnamed: KBR109.1, MX_RGUI_1.3, MX_RGUI_2.3, MX_RGUI_3.3
unnamed: KBR110.1, MX_APP_1.3, MX_APP_2.3
unnamed: KBR111.1, MX_RCTL_1.3, MX_RCTL_2.3
unnamed: KBR112.1, MX_LEFT_1.3
unnamed: KBR113.1, MX_DOWN_1.3
unnamed: KBR114.1, MX_RGHT_1.3
unnamed 255: LED1.2 (A), R6.1; also elsewhere on the board
unnamed 256: LED2.2 (A), R7.1; also elsewhere on the board
unnamed 257: LED3.2 (A), R8.1; also elsewhere on the board
unnamed: LED7.2 (A), R9.1
unnamed: LED8.2 (A), R10.1
unnamed: R3.2, U1.33 ((~HWB~)PE2), U1_2.33 ((~HWB~)PE2)
unnamed: RGBLED1.1 (DOUT), RGBLED2.3 (DIN)
unnamed: RGBLED2.1 (DOUT), RGBLED3.3 (DIN)
unnamed: RGBLED3.1 (DOUT), RGBLED4.3 (DIN)
unnamed: U1.42 (AREF), U1_2.42 (AREF)
VCC: C4.1, C5.1, C6.1, C7.1, C8.1, C9.1, C10.1, C11.1, C12.1, ICSP1.2, J1.1, Q1.2 (S), R4.1, R5.1, R6.2, R7.2, R8.2, RGBLED1.4 (VDD), RGBLED2.4 (VDD), RGBLED3.4 (VDD), RGBLED4.4 (VDD), U1.2 (UVCC), U1.7 (VBUS), U1.14 (VCC), U1.24 (AVCC), U1.34 (VCC), U1.44 (AVCC), U1_2.2 (UVCC), U1_2.7 (VBUS), U1_2.14 (VCC), U1_2.24 (AVCC), U1_2.34 (VCC), U1_2.44 (AVCC), USB1.1 (VBUS), USB2.1 (VBUS); also elsewhere on the board

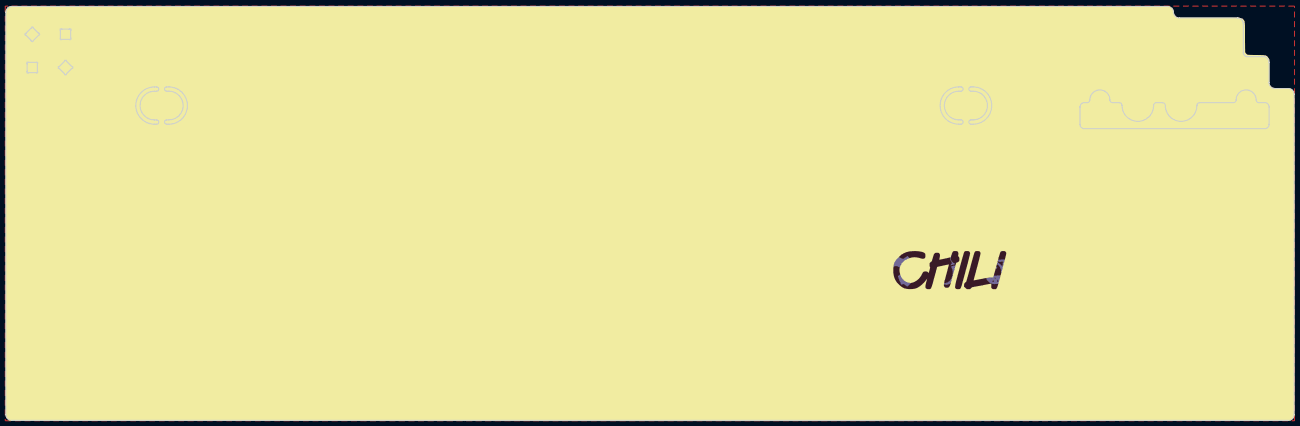
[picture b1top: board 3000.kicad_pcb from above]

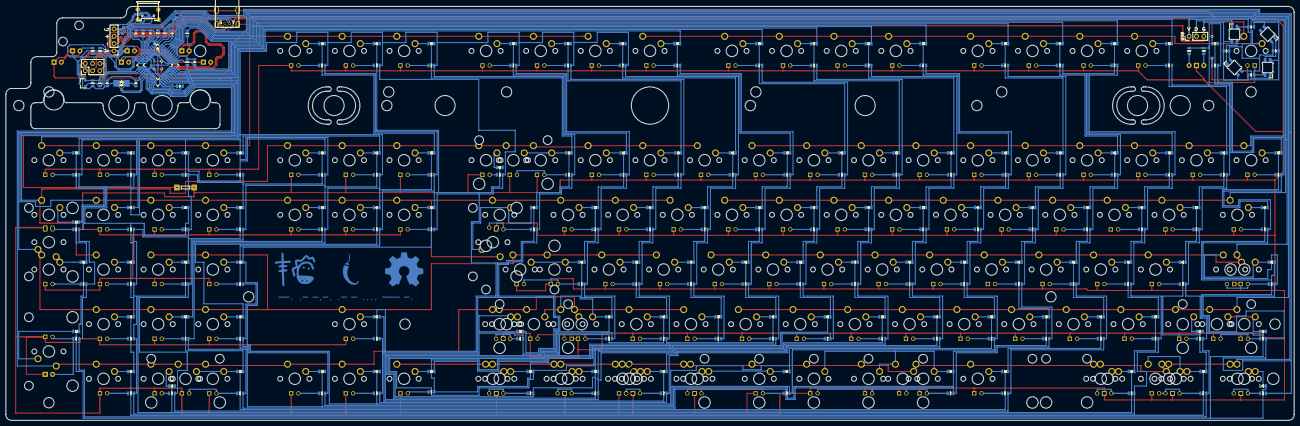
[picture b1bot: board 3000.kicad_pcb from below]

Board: 2 copper layers, 449.1 x 144.3 mm, 397 parts (252 on the bottom side), 266 nets.

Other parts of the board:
LED1#2, LED2#2, LED3#2: 3mm; LED_D3.0mm
RGB: Pin_Header_Straight_1x03_Pitch2.54mm

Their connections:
/LED1: LED1#2.1; also elsewhere on the board
/LED2: LED2#2.1; also elsewhere on the board
/LED3: LED3#2.1, RGB.2; also elsewhere on the board
GND: RGB.3; also elsewhere on the board
unnamed 255: LED1#2.2; also elsewhere on the board
unnamed 256: LED2#2.2; also elsewhere on the board
unnamed 257: LED3#2.2; also elsewhere on the board
VCC: RGB.1; also elsewhere on the board

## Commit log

2017-11-04 upload
    2017.11.04
2017-11-11 draw
